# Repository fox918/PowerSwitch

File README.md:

# SmartPowerSwitch Project

## Idea
Having a simple and extensible way to switch 12V power with up to 10A with a microcontroller.
The intended use for the device is to remotely switch things at amateur radio repeater sites. 

## Concept
The idea is to use a Infineon SmartFET as powerswitch.
This reduces complexity because a lot of things are already taken care of and we can
further use the diagnostic outputs to measure the current.

Using an i2c GPIO expander and an i2c ADC allows for measuring supply voltage, current delivered to the output and temperature of the heatsink.

With a dip switch, we can change the address of both i2c devices simultaneously, therefore allowing 4 devices on the same i2c bus.

Look at [PowerSwitch Idea](./PowerSwitch_Idea.pdf) for a Block Schema.

## Current State
An initial approach of the [Schema](./Circuit_Schema_v2.pdf) and the PCB is done, after review a prototype shall be built.

### Current PCB
- [PCB Front](./PCB_front_v2.png) 
- [PCB_Back](./PCB_back_v2.png) 

### Current Issues
- Almost no protection circuits on the internal voltage source
- Current paths on the pcb not optimal (especially ground path)
- Choose a suitable connector for the i2c backplane (suggestion: rj12, JST SH or some 2.54mm connector)

## Further development
- Design a board to mount the two colored button
- Choose a ethernet enabled microcontroller and design a i2c shield for it 
(and a nice GUI)
- adapt the boards to mount into 1U rackunits with XLR 4-Pin connectors

## License
[MIT, 2017 Oliver Wisler](./LICENSE)

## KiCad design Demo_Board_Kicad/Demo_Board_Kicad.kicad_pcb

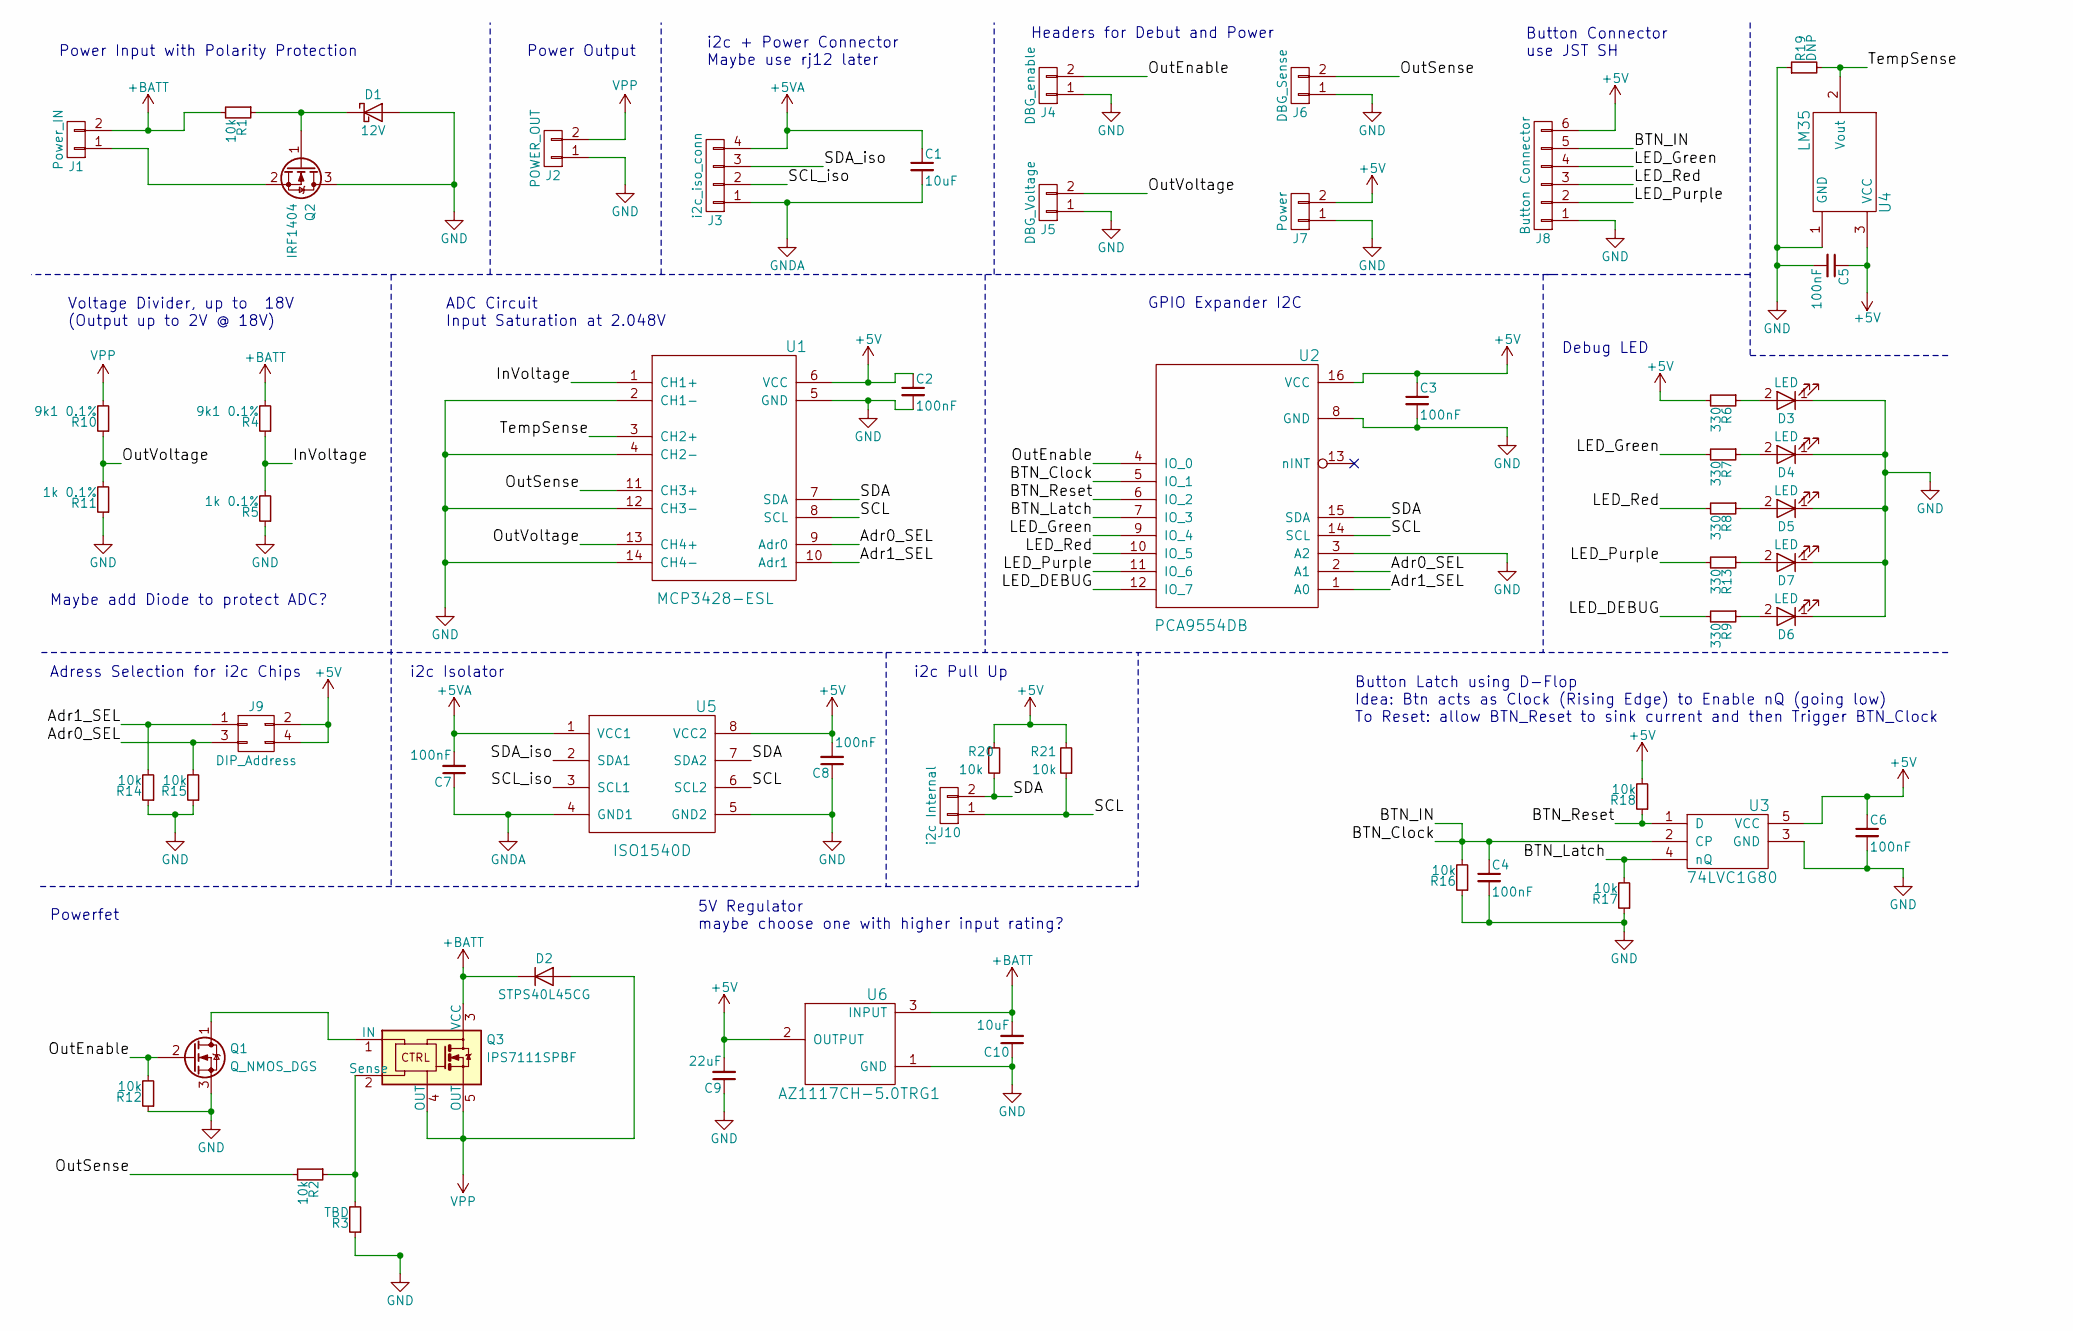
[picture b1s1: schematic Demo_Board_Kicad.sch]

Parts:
C1, C10: 10uF; C_0603_HandSoldering
C2, C3, C4, C5, C6, C7, C8: 100nF; C_0603_HandSoldering
C9: 22uF; C_0603_HandSoldering
D1: 12V; D_SOD-323F
D2: STPS40L45CG; TO-263-2
D3, D4, D5, D6, D7: LED; LED_0603_HandSoldering
J1: Power_IN; PowerPole2P
J2: POWER_OUT; PowerPole2P
J3: i2c_iso_conn; Pin_Header_Straight_1x04_Pitch2.54mm
J4: DBG_enable; Pin_Header_Straight_1x02_Pitch2.54mm
J5: DBG_Voltage; Pin_Header_Straight_1x02_Pitch2.54mm
J6: DBG_Sense; Pin_Header_Straight_1x02_Pitch2.54mm
J7: Power; Pin_Header_Straight_1x02_Pitch2.54mm
J8: Button Connector; JST_SH_BM06B-SRSS-TB_06x1.00mm_Straight
J9: DIP_Address; DIP-6_W7.62mm_SMD
J10: i2c Internal; Pin_Header_Straight_1x02_Pitch2.54mm
Q1: Q_NMOS_DGS; SOT-223-3Lead_TabPin2
Q2: IRF1404; TO-263-2
Q3: IPS7111SPBF; TO-263-4
R1, R2, R12, R14, R15, R16, R17, R18, R20, R21: 10k; R_0603_HandSoldering
R3: TBD; R_0603_HandSoldering
R4, R10: 9k1 0.1%; R_0603_HandSoldering
R5, R11: 1k 0.1%; R_0603_HandSoldering
R6, R7, R8, R9, R13: 330; R_0603_HandSoldering
R19: DNP; R_0603_HandSoldering
U1: MCP3428-ESL; SOIC-14_3.9x8.7mm_Pitch1.27mm
U2: PCA9554DB; SSOP-16_5.3x6.2mm_Pitch0.65mm
U3: 74LVC1G80; SOT-353_SC-70-5_Handsoldering
U4: LM35; TO-92_Inline_Narrow_Oval
U5: ISO1540D; SOIC-8_3.9x4.9mm_Pitch1.27mm
U6: AZ1117CH-5.0TRG1; SOT-223-3Lead_TabPin2

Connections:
+5V: C2.1, C3.1, C5.1, C6.1, C8.2, C9.2, J7.2, J8.6, J9.2, J9.4, R6.2, R18.2, R20.1, R21.2, U1.6 (VCC), U2.16 (VCC), U3.5 (VCC), U4.3 (VCC), U5.8 (VCC2), U6.2 (OUTPUT)
+5VA: C1.1, C7.2, J3.4, U5.1 (VCC1)
+BATT: C10.2, D2.1 (K), J1.2, Q3.3 (VCC), R1.2, R4.2, U6.3 (INPUT)
/Adr0_SEL: J9.3, R15.2, U1.9 (Adr0), U2.2 (A1)
/Adr1_SEL: J9.1, R14.2, U1.10 (Adr1), U2.1 (A0)
/BTN_Clock: C4.1, J8.5, R16.2, U2.5 (IO_1), U3.2 (CP)
/BTN_Latch: R17.2, U2.7 (IO_3), U3.4 (nQ)
/BTN_Reset: R18.1, U2.6 (IO_2), U3.1 (D)
/InVoltage: R4.1, R5.2, U1.1 (CH1+)
/LED_DEBUG: R9.2, U2.12 (IO_7)
/LED_Green: J8.4, R7.2, U2.9 (IO_4)
/LED_Purple: J8.2, R13.2, U2.11 (IO_6)
/LED_Red: J8.3, R8.2, U2.10 (IO_5)
/OutEnable: J4.2, Q1.2 (G), R12.2, U2.4 (IO_0)
/OutSense: J6.2, R2.2, U1.11 (CH3+)
/OutVoltage: J5.2, R10.1, R11.2, U1.13 (CH4+)
/SCL: J10.1, R21.1, U1.8 (SCL), U2.14 (SCL), U5.6 (SCL2)
/SCL_iso: J3.2, U5.3 (SCL1)
/SDA: J10.2, R20.2, U1.7 (SDA), U2.15 (SDA), U5.7 (SDA2)
/SDA_iso: J3.3, U5.2 (SDA1)
/TempSense: R19.2, U1.3 (CH2+), U4.2 (Vout)
GND: C2.2, C3.2, C4.2, C5.2, C6.2, C8.1, C9.1, C10.1, D1.2 (A), D3.1 (K), D4.1 (K), D5.1 (K), D6.1 (K), D7.1 (K), J2.1, J4.1, J5.1, J6.1, J7.1, J8.1, Q1.3 (S), Q2.3 (D), R3.1, R5.1, R11.1, R12.1, R14.1, R15.1, R16.1, R17.1, R19.1, U1.2 (CH1-), U1.4 (CH2-), U1.5 (GND), U1.12 (CH3-), U1.14 (CH4-), U2.3 (A2), U2.8 (GND), U3.3 (GND), U4.1 (GND), U5.5 (GND2), U6.1 (GND)
GNDA: C1.2, C7.1, J3.1, U5.4 (GND1)
unnamed: D1.1 (K), Q2.1 (G), R1.1
unnamed: D3.2 (A), R6.1
unnamed: D4.2 (A), R7.1
unnamed: D5.2 (A), R8.1
unnamed: D6.2 (A), R9.1
unnamed: D7.2 (A), R13.1
unnamed: J1.1, Q2.2 (S)
unnamed: Q1.1 (D), Q3.1 (IN)
unnamed: Q3.2 (Sense), R2.1, R3.2
VPP: D2.2 (A), J2.2, Q3.4 (OUT), Q3.5 (OUT), R10.2

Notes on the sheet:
Power Input with Polarity Protection
Voltage Divider, up to 18V (Output up to 2V @ 18V)
Power Output
i2c + Power Connector Maybe use rj12 later
Button Connector use JST SH
Debug LED
Headers for Debut and Power
Maybe add Diode to protect ADC?
ADC Circuit Input Saturation at 2.048V
GPIO Expander I2C
Button Latch using D-Flop Idea: Btn acts as Clock (Rising Edge) to Enable nQ (going low) To Reset: allow BTN_Reset to sink current and then Trigger BTN_Clock
Adress Selection for i2c Chips
i2c Isolator
i2c Pull Up
Powerfet
5V Regulator maybe choose one with higher input rating?

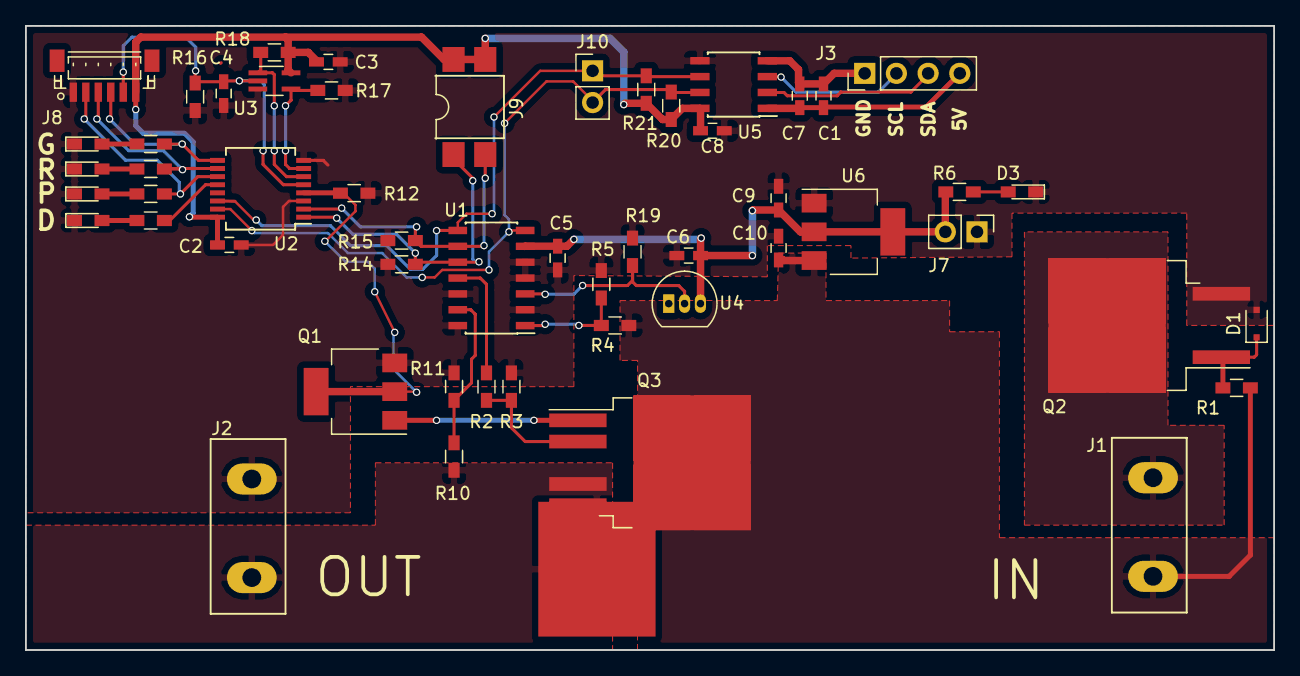
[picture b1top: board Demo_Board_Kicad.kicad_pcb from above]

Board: 2 copper layers, 100.0 x 50.0 mm, 54 parts (1 on the bottom side), 33 nets.

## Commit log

2017-09-07 created block schema
2017-09-07 relayout
2017-09-07 searched parts
2017-09-11 cleanup files
2017-09-11 added readme and license
2017-09-11 extended readme
2017-09-11 rotated pdfs
2017-09-14 added datasheets
2017-09-14 reworked pcb and added new files
2017-09-14 changed readme
2017-09-14 fixed readme with wrong filenames
